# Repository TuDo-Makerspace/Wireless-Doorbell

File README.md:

# TU-DO Wireless Doorbell <!-- omit in toc -->

A wireless doorbell based on the ESP8266

## Table Of Contents <!-- omit in toc -->

- [Overview](#overview)
	- [Doorbell Board](#doorbell-board)
	- [Receiver Board](#receiver-board)
- [Gerbers, BOMs, and Assembly](#gerbers-boms-and-assembly)
- [Configuring the Firmware and Flashing the Boards](#configuring-the-firmware-and-flashing-the-boards)
- [Firmware Structure](#firmware-structure)
- [License](#license)

## Overview

The TU-DO Wireless Doorbell is an open source and open hardware doorbell which runs over WiFi. The project utilizes the ESP8266 microcontroller, and includes two boards, one for the doorbell button and the other for the receiver.

### Doorbell Board

The doorbell board (also refered to as the "Door" board) is designed to be placed at the door and features a button to trigger the doorbell ring. It is powered by a 9V battery for easy installation.

The circuit of the doorbell board consists of:
- A button for triggering the doorbell ring
- Two indicator LEDs (one red and one green)
- An ESP8266 microcontroller
- A 9V battery
- A MOSFET power latch

When the ring button is pressed, power is supplied to the ESP8266 and the power latch is activated. The ESP8266 then connects to the WiFi network and sends a TCP packet to all receivers. After successful transmission, the power latch is unlatched and the device fully powers down. With normal usage, a 9V battery should last for multiple months.

During normal operation, the two indicator LEDs provide the following feedback to the user:
- The red LED indicates that the ESP8266 is powered
- The green LED indicates a successful transmission of the TCP packet

In case of an error however, the indicators are used for troubleshooting and will flash in a specific pattern, as described in the following table:

| LED Flash Pattern 				| Error 											|
|-----------------------------------------------|-----------------------------------------------------------------------------------------------|
| Power LED flashes 6x, Connection LED Off 	| Invalid `DoorCFG` provided (This can only occur if the Firmware code has been modified) 	|
| Power LED & Connection LED flash 3x 		| WiFi connection failed 									|
| Power LED flashes 3x, Connection LED Off 	| Failed to ring all Bells (Receivers) 								|
| Power LED & Connection LED flash 3x 		| Some, but not all Bells (Receivers) rang 							|
| Power LED & Connection LED flash alternately 	| `Door` class object improperly initialized (This can only occur if the Firmware code has been modified) |

For further debugging, the ESP8266 will also print a detailed log over the USB serial monitor at `115200` baud.

### Receiver Board

One or more receiver boards (also refered to as the "Bell" boards) are placed at locations where the doorbell ring is to be heard, and feature a buzzer for playing the doorbell ringtone. The receiver is continuously powered by a 5V-12V power supply and acts as a server, waiting for TCP packets from the doorbell board.

The circuit of the receiver board consists of:
- A buzzer for playing the doorbell ringtone
- A red power indicator LED
- A white ring indicator LED
- An ESP8266 microcontroller
- An optional power MOSFET (for driving a higher voltage ring indicator light, which would require a higher voltage power supply such as 12V)

When the ESP8266 on the receiver board receives a TCP packet from the doorbell board, it will play the doorbell ringtone on the buzzer and flash the white ring indicator LED to provide visual feedback.

Additionally, if an error occurs, the ring indicator LED and the buzzer are used for troubleshooting, as described in the following table:

| LED Flash Pattern 				   	    | Error 												      |
|-----------------------------------------------------------|---------------------------------------------------------------------------------------------------------|
| LED continously flashes slowly, Buzzer is silent	    | No WiFi connection, the device is attempting to (re-)connect to the WiFi network			      |
| LED continously flashes quickly (250ms), Buzzer is silent | Invalid `BellCFG` provided (This can only occur if the Firmware code has been modified) 		      |
| LED continously flashes quickly (250ms), Buzzer beeps	    | `Bell` class object improperly initialized (This can only occur if the Firmware code has been modified) |

For further debugging, the ESP8266 will also print a detailed log over the USB serial monitor at `115200` baud.

## Gerbers, BOMs, and Assembly

The Gerber files for the doorbell and receiver boards can be found in the `kicad/(BOARD)/gerbers` folder. An Interactive Bill Of Materials (IBOM) for the Door board is available [here](https://TU-DO-Makerspace.github.io/Wireless-Doorbell/door-ibom.html) and for the Bell board [here](https://TU-DO-Makerspace.github.io/Wireless-Doorbell/bell-ibom.html). These provide not only a list of all components, but also a visual representation of the PCB layout, showing where each component is placed. This can be particularly useful during the assembly process.

The PCB design utilizes many JST connectors, making it easy to incorporate the device into a variety of enclosures. If you have access to a 3D printer, you can also print the enclosures provided in the `STL` folder.

## Configuring the Firmware and Flashing the Boards

The firmware for the doorbell and receiver boards has been written using PlatformIO, and it is highly recommended to use it for flashing the boards. Before flashing the firmware, you need to configure all necessary settings such as WiFi credentials, the static door IP, the number of receivers, etc. in the `src/config.h` header file.

> **Important Note on IP Addresses:** The current version of the firmware requires all boards to have a static IP address, and the IP addresses of the receiver boards must be incremented after the doorbell board's IP. For example, if the doorbell board has IP `192.168.0.20`, the first receiver board must have IP `192.168.0.21`, the second receiver board must have IP `192.168.0.22`, and so on.

The IP addresses for the receiver boards can be configured in the [platformio.ini](platformio.ini) file. Currently, the targets are set up for the TU-DO Makerspace's network, but they can easily be changed to match your own setup.

To flash the boards, follow these steps:
1. Select the corresponding target in PlatformIO.
2. Remove the ESP8266 from the board that you wish to flash.
3. Connect the ESP8266 to your computer.
4. Click the upload button in PlatformIO.

> Note: Flashing the ESP8266 while it is inside the board may not work properly, so it is recommended to remove the ESP8266 from the board before flashing.

## Firmware Structure

The firmware code is organized in the `src` folder and is comprised of three main parts: `bell`, `door`, and `common`. The code for the doorbell and receiver boards is located in the `door` and `bell` folders, respectively, while code shared between the two is stored in the `common` folder.

> Note: A PDF of the class diagram can be found [here](pdf/ClassDiagram.pdf).

The firmware was written in an object-oriented manner and heavily utilizes state machines. Each device is controlled by a main class such as `Door` for the doorbell and `Bell` for the receiver. These classes are then made up of subclasses that handle smaller tasks, such as the `Buzzer` class that manages the buzzer on the receiver and the `RingSender` class that handles the sending of TCP packets from the doorbell.

> Note: A PDF of the state diagram can be found [here](pdf/StateDiagram.pdf).

The codebase also generates a doxygen documentation that can be found [here](https://TU-DO-Makerspace.github.io/Wireless-Doorbell).

To fully comprehend the code, we highly recommend reading the comments within the code as well as consulting the doxygen documentation. Although we've endeavored to make the code self-explanatory and provided ample comments, feel free to reach out if you have any questions by opening an issue (make sure to include "QUESTION" in the issue title).

## License

The TU-DO Wireless Doorbell firmware is licensed under the GPLv3 license. The hardware is licensed under the TAPR Open Hardware License v2.0.

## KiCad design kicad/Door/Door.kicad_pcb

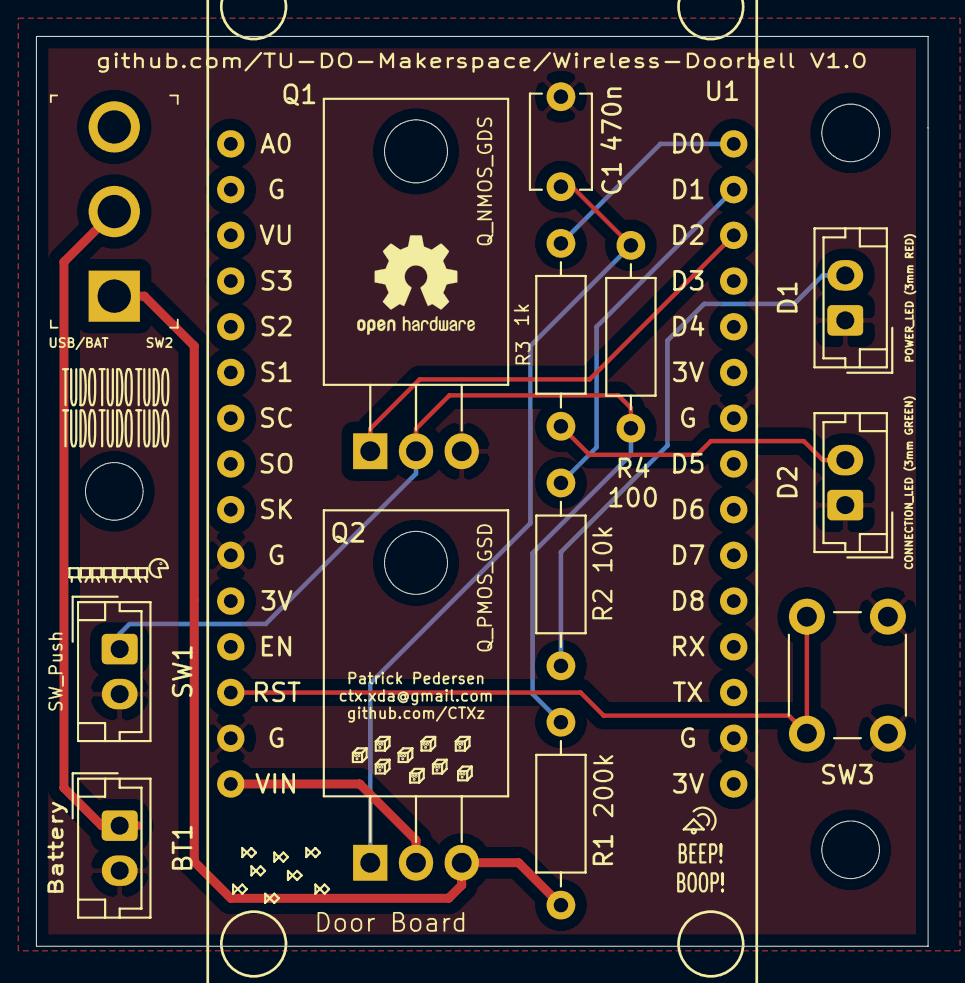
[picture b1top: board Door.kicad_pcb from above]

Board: 2 copper layers, 49.5 x 50.5 mm, 14 parts (0 on the bottom side), 12 nets.

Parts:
BT1: Battery; JST_EH_B2B-EH-A_1x02_P2.50mm_Vertical
C1: 470n; C_Disc_D5.1mm_W3.2mm_P5.00mm
D1: POWER_LED (3mm RED); JST_EH_B2B-EH-A_1x02_P2.50mm_Vertical
D2: CONNECTION_LED (3mm GREEN); JST_EH_B2B-EH-A_1x02_P2.50mm_Vertical
Q1: Q_NMOS_GDS; TO-220-3_Horizontal_TabDown
Q2: Q_PMOS_GSD; TO-220-3_Horizontal_TabDown
R1: 200k; R_Axial_DIN0207_L6.3mm_D2.5mm_P10.16mm_Horizontal
R2: 10k; R_Axial_DIN0207_L6.3mm_D2.5mm_P10.16mm_Horizontal
R3: 1k; R_Axial_DIN0207_L6.3mm_D2.5mm_P10.16mm_Horizontal
R4: 100; R_Axial_DIN0207_L6.3mm_D2.5mm_P10.16mm_Horizontal
SW1: SW_Push; JST_EH_B2B-EH-A_1x02_P2.50mm_Vertical
SW2: USB/BAT; Toggle_Switch_100SP1T1B4M2QE
SW3: RST_BTN; SW_PUSH_6mm
U1: NODEMCU v3; NodeMCU-LoLinV3

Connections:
9V_BAT_+: Q2.3, R1.2, SW2.1
CONNECTION_LED: R3.1, U1.30
GND: BT1.2, C1.2, D1.1, D2.1, Q1.3, SW1.2, SW3.2, U1.10, U1.14, U1.17, U1.24
NODE_VIN: Q2.2, U1.15
unnamed: BT1.1, SW2.2
unnamed: C1.1, Q2.1, R4.2
unnamed: D1.2, R2.2
unnamed: D2.2, R3.2
unnamed: Q1.2, R1.1, R4.1, SW1.1
POWER_LATCH: Q1.1, U1.28
POWER_LED: R2.1, U1.29
RST_BTN: SW3.1, U1.13

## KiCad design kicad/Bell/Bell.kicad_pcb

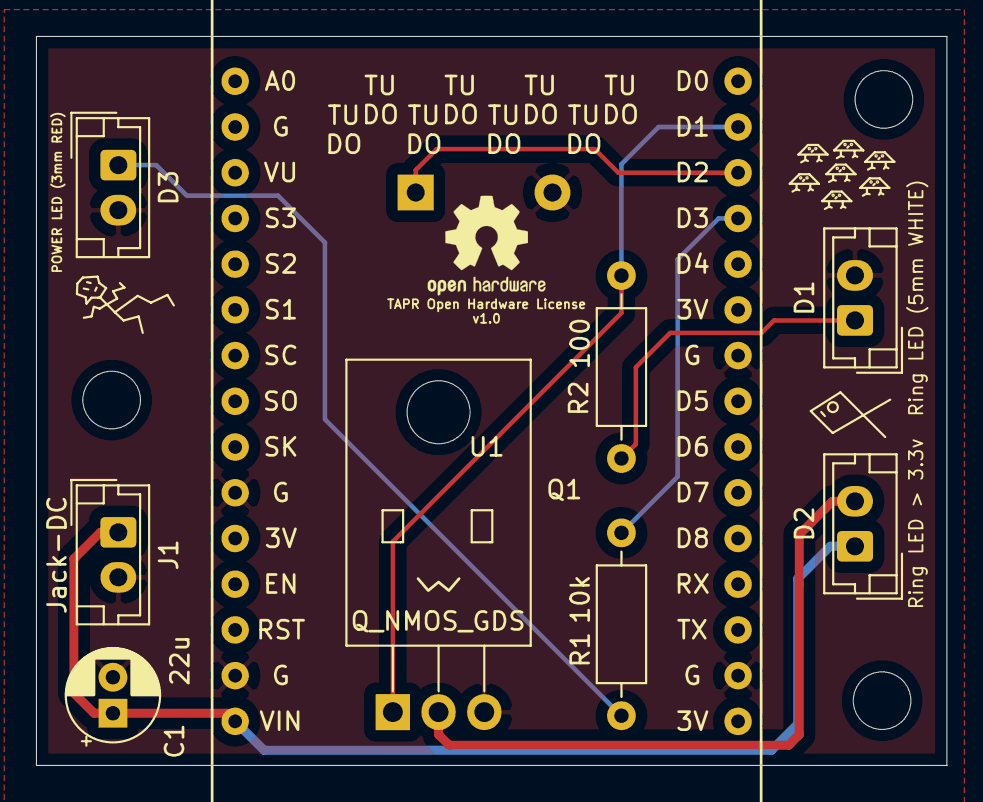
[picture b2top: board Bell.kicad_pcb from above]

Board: 2 copper layers, 50.6 x 40.5 mm, 10 parts (1 on the bottom side), 8 nets.

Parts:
BZ1: Buzzer; Buzzer_12x9.5RM7.6
C1: 22u; CP_Radial_D5.0mm_P2.00mm
D1: Ring LED (5mm WHITE); JST_EH_B2B-EH-A_1x02_P2.50mm_Vertical
D2: Ring LED > 3.3v; JST_EH_B2B-EH-A_1x02_P2.50mm_Vertical
D3: POWER LED (3mm RED); JST_EH_B2B-EH-A_1x02_P2.50mm_Vertical
J1: Jack-DC; JST_EH_B2B-EH-A_1x02_P2.50mm_Vertical
Q1: Q_NMOS_GDS; TO-220-3_Horizontal_TabDown
R1: 10k; R_Axial_DIN0207_L6.3mm_D2.5mm_P10.16mm_Horizontal
R2: 100; R_Axial_DIN0207_L6.3mm_D2.5mm_P10.16mm_Horizontal
U1: NodeMCUv3; NodeMCU-LoLinV3

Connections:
GND: BZ1.2, C1.2, D1.2, D3.2, J1.2, Q1.3, U1.10, U1.14, U1.17, U1.24
unnamed: D1.1, R2.1
unnamed: D2.2, Q1.2
unnamed: D3.1, R1.1
POWER_LED: R1.2, U1.27
RING_BUZZER: BZ1.1, U1.28
RING_LED: Q1.1, R2.2, U1.29
VCC: C1.1, D2.1, J1.1, U1.15

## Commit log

2021-10-24 SQUASH: Log: Improved serial out logging Beacon: SSID, PWD and timeout are now set in the constructor Beacon: Fixed status() still returning TIMEOUT after calling stop() Scanner: SSID and PWD are now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
2021-10-24 Log: Added GPLv3 Header
2021-10-29 Main_Door: Keep power LED on until full shut down Main_Door: Added LATCH_POWER and UNLATCH_POWER macros
2021-10-29 extra_script: Remove --before opt in UPLOADCMD as its already provided by UPLOADERFLAGS
2021-10-30 Added possibility to provide a password file for the AP password
2021-11-01 Beacon: Hide network on non-debug builds Main_Door: Added power logs
2021-11-01 Build: Made mkpwd.sh executable
2021-11-01 mkpwd: Fixed passwords being too long
2021-11-01 extra_script: Define HOST_AP_PWD and SCAN_AP_PWD
2021-11-01 Main_Door: Improved Power Unlatch log message
2021-11-01 mkpwd: Limit password to A-Z0-9
2021-11-01 Main_Bell: Start beacon before starting ring to avoid delays during ringing
2021-11-01 Main_Door: Stop beacon on device shut-down to give bells enough time to confirm connection
2021-11-02 See Description Main_Bell: Increased HOST_BEACON_TIMEOUT to 20s Main_Bell: Added seperate function to handle forward beacon Main_Bell: Added MIN_SPOT_TIME to ensure receiver can confirm successfull c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
2021-11-05 added melody
2021-11-05 Bell: Updated Melody
2021-11-05 new structure
2021-11-06 Bell: Added possibility to choose between melodies
2021-11-30 Added Schematics
2021-12-06 Main_Door: Fixed typo
2021-12-06 Main_Bell: Use DEFAULT_CHIME as melody if melody has not been provided in compiler defines
2021-12-06 PCB: Door: Set pull-up resistor to 200k to give ESP enough time to boot
2021-12-06 Platformio: Distinguish SSIDs for DEBUG builds to avoid ringing real bell when debugging
2021-12-07 PCB: Added PCB for Door board
2022-01-06 Kicad: Finished 1st PCB revision
2022-01-25 Kicad: Updated to v6.0
2022-10-15 Initial commit of SW revision 2.0.0_ALPHA
    Software revision 2.0.0 no longer operates decentralized, but instead
    now makes use of a local network connection.
    Bells:
    The bells are constantly connected to our wireless network and await a
    TCP package from the door. Once a valid TCP package has been received,
    the bell will ring.
2022-10-15 Bell: Implemented update method pattern + Handle LED flashing
2022-10-16 Added a Mutex class to prevent mutual access on peripherals (ex. the LED)
2022-10-16 Main_Bell: Do not perform ip check in debug build
    During debugging it is often desired to send tcp packets from
    any host device.
2022-10-16 Updated gitignore
2022-10-16 Main_Bell: Fixed on_connect constantly getting executed
2022-10-16 Bell: Keep LED on during ring instead of flashing it
    Epileptics will love this commit
2022-10-16 Added WiFi monitor class to handle wifi connect and disconnect events
2022-10-16 Door: Addeed DoorUXHandler
    Potentially might rename this into door LED handler or something. It's current job is
    to asynchronously handle the LEDs on the door.
    I'm not too happy with this solution but it's better than the spaghetti code in the Main_Door.cpp file
    before
2022-10-16 Removed mkpwd.sh
    We no longer need to generate passwords in v2.0.0
2022-10-16 DoorUXHandler: Fixed bells_remaining not decrementing to 0
2022-10-16 Door: Fixed device remaining on if no WiFi connection can be established
2022-10-17 Split code into bell, door and common directory
2022-10-17 Renamed DoorUXHandler to DoorUX
2022-10-17 Renamed Bell to BellUX
2022-10-25 v2.1.0: Major refactor of door code
    The door code has been completely overhauled and now consists of a main
    Door class, which is configured by a DoorCFG object, as well has a WiFiHandler class, a RingSender class and
    a RingTX class.
    To ensure processes run "asynchronously", all classes are implemented as state machines.
    Door
    ----
2022-10-31 DoorCFG: Validate subnet and gateway
2022-11-20 WiFiHandler: Added rejoin parameter which will not call WiFi.disconnect() on unexpected disconnects
2022-11-20 Bell: v2.1.0: Major refactor of bell code
    This commit is the second part of our major refactor.
    This time the bell code has been overhauled in similar manner to the
    door code.
    A main Bell class has been created, which is initialized by a BellCFG
    class. WiFi handling is now managed through the shared WiFiHandler.
    Ring receiving is handled by the RingReceiver class and the buzzer
2022-11-20 Door: Fixed condition for fallback error
2022-11-20 Reformatted some switch statements
2022-11-20 Dropped Mutex class
2022-11-21 Removed BellUX header
2022-11-21 Added copyright header
2022-11-21 Door: Update wifi handler and ring sender at end of every run() loop
2022-11-24 Docs: Documented code + Minor code re-arrangements and fixes
2022-11-24 Added doxygen
2023-02-13 README: Initial concept for README.md
2023-02-13 README: Parsed through ChatGPT, thank you my beloved
2023-02-15 README: Added images
2023-02-16 Door: Disconnect from wifi during power-off
2023-02-16 README/Docs: Added Diagrams
2023-02-16 README: Upadted Door schematic to be more consistent
2023-02-17 README: Added error tables
2023-02-17 README: Added link for Doxygen GH Pages
2023-02-17 PCBs: Added iboms
2023-02-17 README: Clarify that there can be multiple Bell boards
2023-02-17 README: Minor change
2023-02-17 Git: Fixed submodule
2023-02-20 Kicad: Updated Schematics and PCBs to Kicad v7.0
2023-02-21 README: Added TOC + Minor changes

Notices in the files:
kicad/Bell/Bell.kicad_pcb:
License: TAPR Open Hardware License v1.0
